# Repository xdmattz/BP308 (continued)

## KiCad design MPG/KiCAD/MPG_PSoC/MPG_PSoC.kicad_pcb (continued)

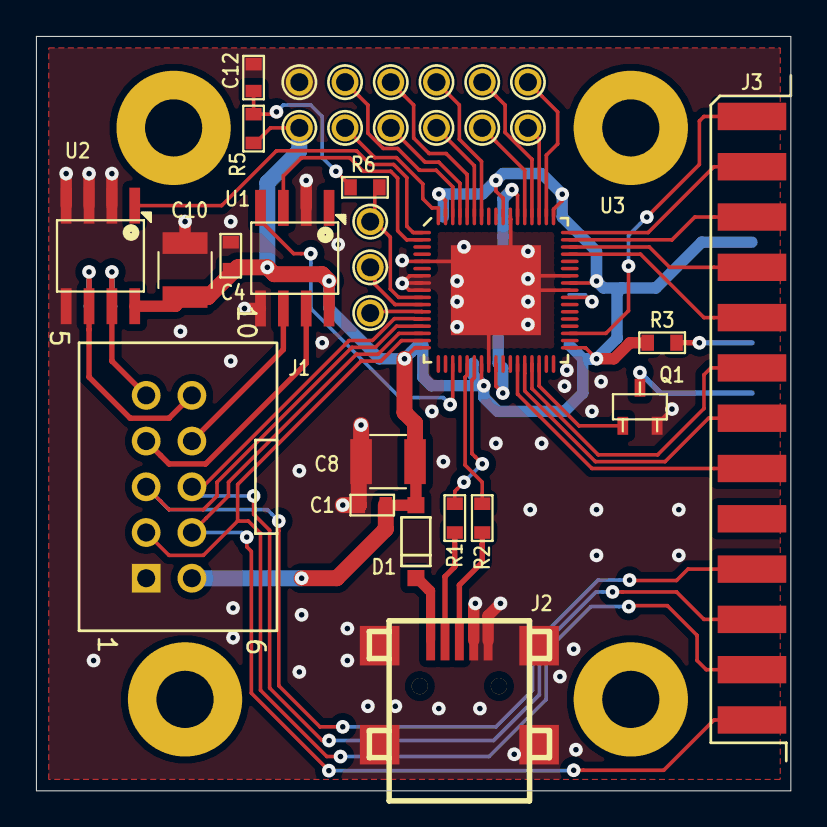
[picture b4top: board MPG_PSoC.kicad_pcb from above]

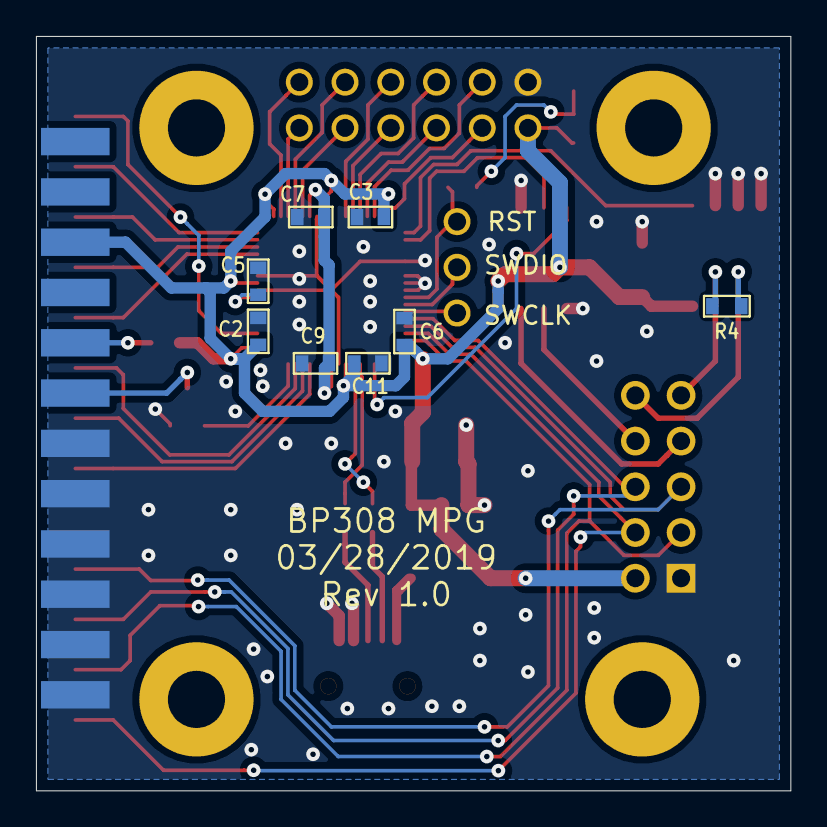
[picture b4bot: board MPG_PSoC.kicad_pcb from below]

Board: 2 copper layers, 41.9 x 41.9 mm, 41 parts (8 on the bottom side), 45 nets.

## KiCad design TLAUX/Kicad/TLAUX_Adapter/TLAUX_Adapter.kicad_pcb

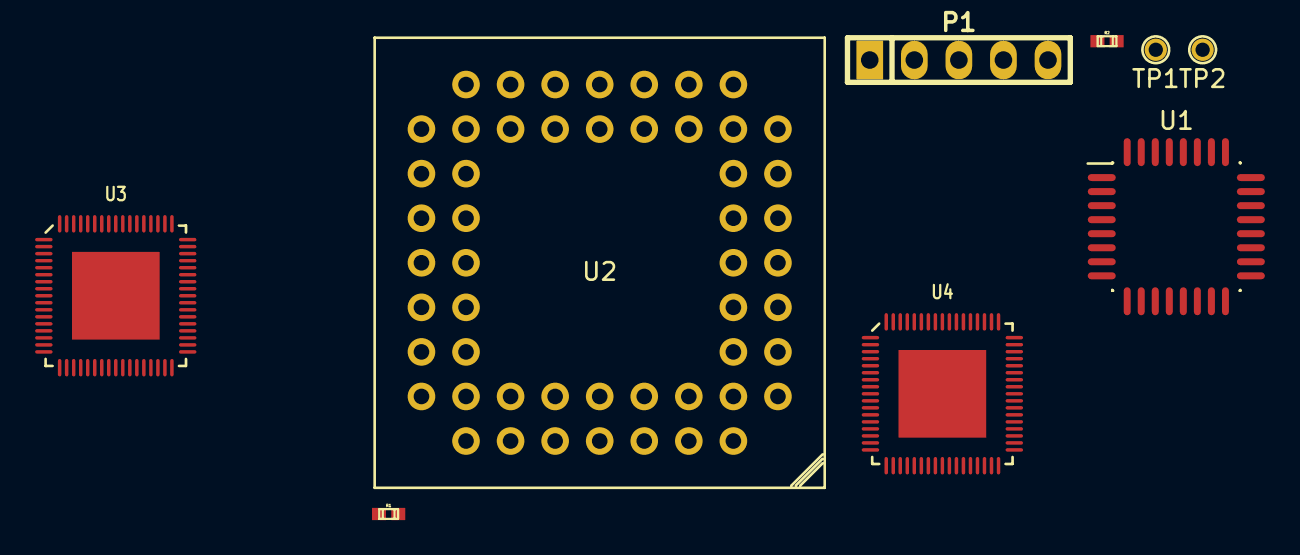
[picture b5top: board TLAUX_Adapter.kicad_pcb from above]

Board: 2 copper layers, 9 parts (0 on the bottom side), 7 nets, no tracks yet.

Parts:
P1: CONN_01X05; pin_strip_5
R1, R2: 4.7K; r_0402
TP1, TP2: TP; TP50
U1: ATMEGA328PB-AU; QFP-32_7x7_Pitch0.8mm
U2: MC68HC811E2; PLCC_52_Socket
U3: CY8C58LP_QFN68; QFN_68
U4: CY8C4246LTI-M445; QFN_68

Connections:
/RST: P1.3, U3.10
/SWDCLK: P1.4, U3.12
/SWDIO: P1.5, U3.11
/VDDD: P1.1, R1.1, R2.1, U3.17, U3.35, U3.67
I2C_SCL_ARM: R2.2, TP1.1, U3.3
I2C_SDA_ARM: R1.2, TP2.1, U3.4
unnamed: U3.5, U3.7, U3.8, U3.9

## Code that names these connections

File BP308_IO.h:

#ifndef BP308_IO_H
#define BP308_IO_H

// definitions for the IO ports on the DANALOG Board for the Bridgeport Discovery 308 rebuild
// The DANALOG board looks like both a KANALOG and KONNECT board
// 
// 
// KANALOG Connections
//
// Inputs
#define ESTOP			    128		// ESTOP Switch - OPTO_0
#define SPINDLE_FAULT	    129		// Pins - need to double check the name here - OPTO_1
#define POWER_MODULE_READY  130	// - OPTO_2
#define AXIS_FAULT		    131		// - OPTO_3
#define X_LIMIT			    132		// Normally Closed - OPTO_4
#define X_HOME			    134		// Normally Open - OPTO_6
#define Y_LIMIT			    133		// Normally Closed - OPTO_5
#define Y_HOME			    135		// Normally Open - OPTO_7
#define Z_LIMIT			    136		// Normally Closed - OPTO_8
#define Z_HOME			    138		// Normally Open - OPTO_10
#define OPTO_9			    137		// UNUSED - OPTO_9
#define HEAD_WHITE		    139		// OPTO_11
#define HEAD_RED		    140		// OPTO_12
#define HEAD_GREEN		    141		// OPTO_13
#define HEAD_BLUE		    142		// OPTO_14
#define HEAD_YELLOW		    143		// OPTO_15
#define TOOL_RELEASE        143     // same as yellow wire.

#define ESTOP_ACTIVE	    1		// Reads 1 when the ESTOP switch is pressed
#define ESTOP_RUN           0
#define ESTOP_OK            0
#define SPINDLE_FAULTED     0       // Double Check all of these!!!
#define SPINDLE_FAULT_OK    1
#define POWER_MODULE_OK     1
#define AXIS_FAULTED        1
#define AXIS_FALT_OK        0
#define X_AT_LIMIT          0
#define X_NO_LIMIT          1
#define X_AT_HOME           1
#define Y_AT_LIMIT          0
#define Y_NO_LIMIT          1
#define Y_AT_LIMIT          0
#define Y_AT_HOME           1
#define Z_AT_LIMIT          0
#define Z_NO_LIMIT          1
#define Z_AT_LIMIT          0
#define Z_AT_HOME           1


// Outputs
// 24V FET drive
#define ESTOP_RELAY		    152		// 24V FET 0
#define SPINDLE_ENABLE 	    153 	// 24V FET 1
#define RELAY3			    154		// 24V FET 2
#define Z_BRAKE			    155		// 24V FET 3
#define FET4			    156
#define FET5			    157
#define FET6			    158
#define FET7			    159

// Isolated AC Control
// the first four AC controls are 110V
#define OIL_LUBE		    160		// AC0 Bijur oiler
#define FLOOD_MOTOR		    161		// AC1 Flood coolant relay control
#define DOOR_FAN		    162		// AC2 electronic cabinet door fan
#define AC3_110			    163		// available				
// the other 4 AC controls are 220V
#define AC4_220			    164		// no triac installed
#define AC5_220			    165		// no triac installed
#define AC6_220			    166		// available
#define AC7_220			    167		// available

// Other Kanalog Connections
// Analog Outputs
// DAC 0 - X_AXIS
// DAC 1 - Y_AXIS
// DAC 2 - Z_AXIS
// DAC 3 - A_AXIS - currently not connected to anything
// DAC 4 - open
// DAC 5 - open
// DAC 6 - open
// DAC 7 - SPINDLE

// Analog Inputs
// ADC 0 - 8 currently unused

// Encoder inputs
// Encoder 0 X_Axis
// Encoder 1 Y_Axis
// Encoder 2 Z_Axis
// Encoder 3 A_Axis - currently not connected
// Encoder 4 NU
// Encoder 5 NU
// Encoder 6 NU
// Encoder 7 SPINDLE

// KONNECT Connections
// Extended IO
#define ENC_X_R		    1024	// X_Axis Index
#define ENC_Y_R		    1025	// Y_Axis Index
#define ENC_Z_R		    1026	// Z_Axis Index
#define ENC_A_R		    1027	// A_Axis Index - currently not connected
#define ENC_CH4_R	    1028	//
#define ENC_CH5_R	    1029	//
#define ENC_CH6_R	    1030	//
#define SPINDLE_R	    1031	// Spindle Index
#define MPG_A		    1032	//
#define MPG_B		    1033	//
#define KOUT_1034	    1034	//
#define KOUT_1035	    1035	//
#define KOUT_1036	    1036	//
#define KOUT_1037	    1037	//
#define KOUT_1038	    1038	//
#define KOUT_1039	    1039	//
#define AUX_ISO_0	    1040	//
#define AUX_ISO_1	    1041	//
#define AUX_ISO_2	    1042	//
#define AUX_ISO_3	    1043	//
#define LUBE_MON	    1044	// Lube Oil level
#define COOLANT_MON	    1045	// Coolant motor relay monitor
#define AIR_MON		    1046	// Air input PSI monitor
#define AUX_ISO_7	    1047	//

#define LUBE_MON_OK     1
#define AIR_MON_OK      1
#define COOLANT_MON_OK  1


#endif

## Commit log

2019-11-26 still learning Git. updating with current changes
2019-11-26 added test.txt as a test
2019-11-26 another test
2019-12-28 Added .gitignore
2020-01-18 Added all the files for the BP308 project KiCAD files for all the custom PCBs Code for the TLAUX - tool changer board Code for the MPG - Manual Pulse Generator board Cam files for the Way Covers Pret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
2020-01-18 Removed excess files
2020-01-18 Deleting more excess stuff
2020-01-18 More excess stuff deleted
2020-01-18 Still trying to figure out how to delete stuff
2020-01-18 Deleting more excess files
2020-01-18 More Deletes
2020-01-18 trying to delete
2020-01-18 Deleting Excess files again...
2020-01-18 Still Deleting
2020-01-18 Deleting excess files again.
2020-01-21 BP308 KFLOP Code: Added Limit backoff and Homing
2020-01-22 Did some more axis calculations
2020-01-23 Added BP308 Notes.txt
2020-01-26 Tuned the x, y and z axis. Added plots from KMotion
2020-01-26 Added articles on machine dynamics
2020-01-27 Added Tool Changer Clamp control
2020-01-27 Added Remote Command function
2020-01-30 Adding Spindle Control
2020-02-09 More Spindle work
2020-03-09 Added test interface board to simulate the TLAUX on the test setup
2020-03-26 added alternate spindle control
2020-03-26 changes to allow testbed and machine in the same code
2020-05-10 Working on the KmotionCNC interface
2020-05-11 more stuff
2020-09-12 T3_Test for testing mcode actions
2020-09-14 commit before making major changes to the status reporting
2020-09-16 Changing the way the persist.UserData variables are used learned a bit more about the PC_Comm
2020-09-19 Changed a lot today. Got most of the functions working on the test bed. still need to add spindle control and test it on the real machine.
2020-09-19 BP308_IO.H isn't downloading correctly for some reason...
2020-09-19 Added the spindle check back into BP308_Hardware.c. without it the z axis had problems.
2020-09-19 Sort of working on the machine
2020-09-20 Added Z axis disable check and brake SetBit
2020-09-20 Spindle Measurements
2020-09-21 Some experimentation with thread3
2020-09-21 Having Zaxis startup problems
2020-09-21 Fixed the Z Axis problem by increasing the following error until the axis was initialized the first time.
2020-09-22 Improvements on Spindle Homing
2020-09-28 Trying to figure out why the Z_Axis is giving a fault on power up. Also re-tuned the X and Y axis. they seem to be OK for now.
2020-09-30 I Think the Z Axis is working!
2020-10-03 Getting the Spindle speed control working.
2020-11-02 Added flow chart for interpreter states
2020-11-08 fixing some typos
2020-11-08 Saving in "TESTBED" mode.
2020-11-08 Fixed another typo
2020-11-11 changed the function name SetSpindleRPM to SetRPMSpindle.
2020-11-15 A little work so that the TESTBED works better
2020-11-16 starting tool change commands
2020-11-17 Added commands for the tool changer - P_REMOTE_CMD functions
2020-11-21 Basic Tool Changer commands working!
2020-11-22 minor testing on serial messages
2020-11-27 Added TLAUX Home bit
2020-11-27 Made a TESTBED version of the TLAUX PSoC code to give simulated responses to tool change commands without being attached to the hardware
2020-11-27 Didn't take long to find a bug in the TLAUX TESTBED build! fixed the tool number bug.
2020-11-27 Changed deadzone on spindle PID loop
2020-12-07 Modified the homing algorithm to improve the repeatability.
2020-12-11 Spindle enable testing
2020-12-11 Spindle Testing 2
2020-12-12 push back to testbench
2020-12-14 Spindle Control Refactoring...
2020-12-14 just another change
2020-12-15 Spindle Enable bugs...
2020-12-20 Spindle control bugs...
2020-12-21 Working Tool Changes
2021-06-06 Added a trailing 0x00 to the serial communications
2021-08-21 finally working on some probing routines
2021-08-23 commit test
2021-09-17 fixing the resolution of the MPG to work with both Metric and Imperial
2021-09-17 Got the scaling on the lead screw wrong...
2021-09-19 fixed the MPG 4x issue and added enable switch suport
2021-11-13 Changed some timing on the homing and probing routines for the Z AXIS_FALT_OK
2022-03-11 had some problems with the tool changer changed the tool changer state machine to run at 1ms tweaked a lot of time constants and added a little sensor debounce.
2022-10-13 lowered Z axis acceleration
2022-10-15 Added some diagnostic commands to the kflop code
2022-10-23 updating x and y resolution
